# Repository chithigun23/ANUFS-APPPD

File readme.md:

# ANUFS APPPD

Accelerator pedal position (APPS) and throttle position (TPS) sensor interface for the ANUFS vehicle, with dual-redundant sensing, ignition/electronic-throttle-body kill-switch control, and CAN reporting. A single 8-pin harness connector carries power in, both raw sensor pairs, and the two kill lines out.

## Architecture

- **Power** - the LV battery feed arrives on the shared harness connector, passes through an ideal-diode PFET (Zener-biased) for reverse-polarity/surge protection, and feeds `U6` (LMR33610), which bucks it to 5V. That 5V is diode-ORed with USB-C VBUS onto a single fused node that only ever feeds `U1` (AP2112K-3.3) - the **+3.3V rail is the only supply that leaves the power stage**, reaching the MCU, CAN transceiver, both op-amps and the status LED.
- **Pedal & throttle sensing** - the harness carries two raw accelerator-pedal signals (APPS1/APPS2) and two raw throttle-position signals (TPS1/TPS2), each individually clamped by an automotive `AQ1005-01ETG` TVS array. `U5` and `U7` (`TLV9062` dual op-amps) buffer them with unity gain straight into the MCU's ADC inputs.
- **Compute** - `U2`, an STM32F072CBTx (Cortex-M0), is the hub, clocked from a 24MHz crystal (`Y1`).
- **Shutdown control** - the MCU drives two low-side MOSFETs (`Q1` for ignition, `Q2` for electronic throttle body) that pull the corresponding harness line to ground to trip the external kill relay. Each line has an inline LED (`D3`, `D5`) that lights while its kill switch is active, so the cut state is visible without a laptop. A separate GPIO-driven LED (`LED1`) gives a general board heartbeat/fault indication.
- **Comms** - a `TCAN337` transceiver (`U4`) puts pedal/throttle status and kill-line faults on the vehicle CAN bus via `J4`.
- **Debug & USB** - USB-C (`J5`, ESD-protected by `U3`) for bench debug/firmware and D+/D- to the MCU; `J1` (Conn_SWD) for programming.

The diagram above is a live SVG: dashed lines show active power/signal paths, and the small dots trace the flow through each domain (open `assets/architecture.svg` directly if your viewer doesn't animate it).

## Repo contents

- [KiCad project](apppd.kicad_pro)
- [Schematic](apppd.kicad_sch)
- [PCB layout](apppd.kicad_pcb)
- [Bill of materials](APPPD_DigiKey_BOM.xlsx)

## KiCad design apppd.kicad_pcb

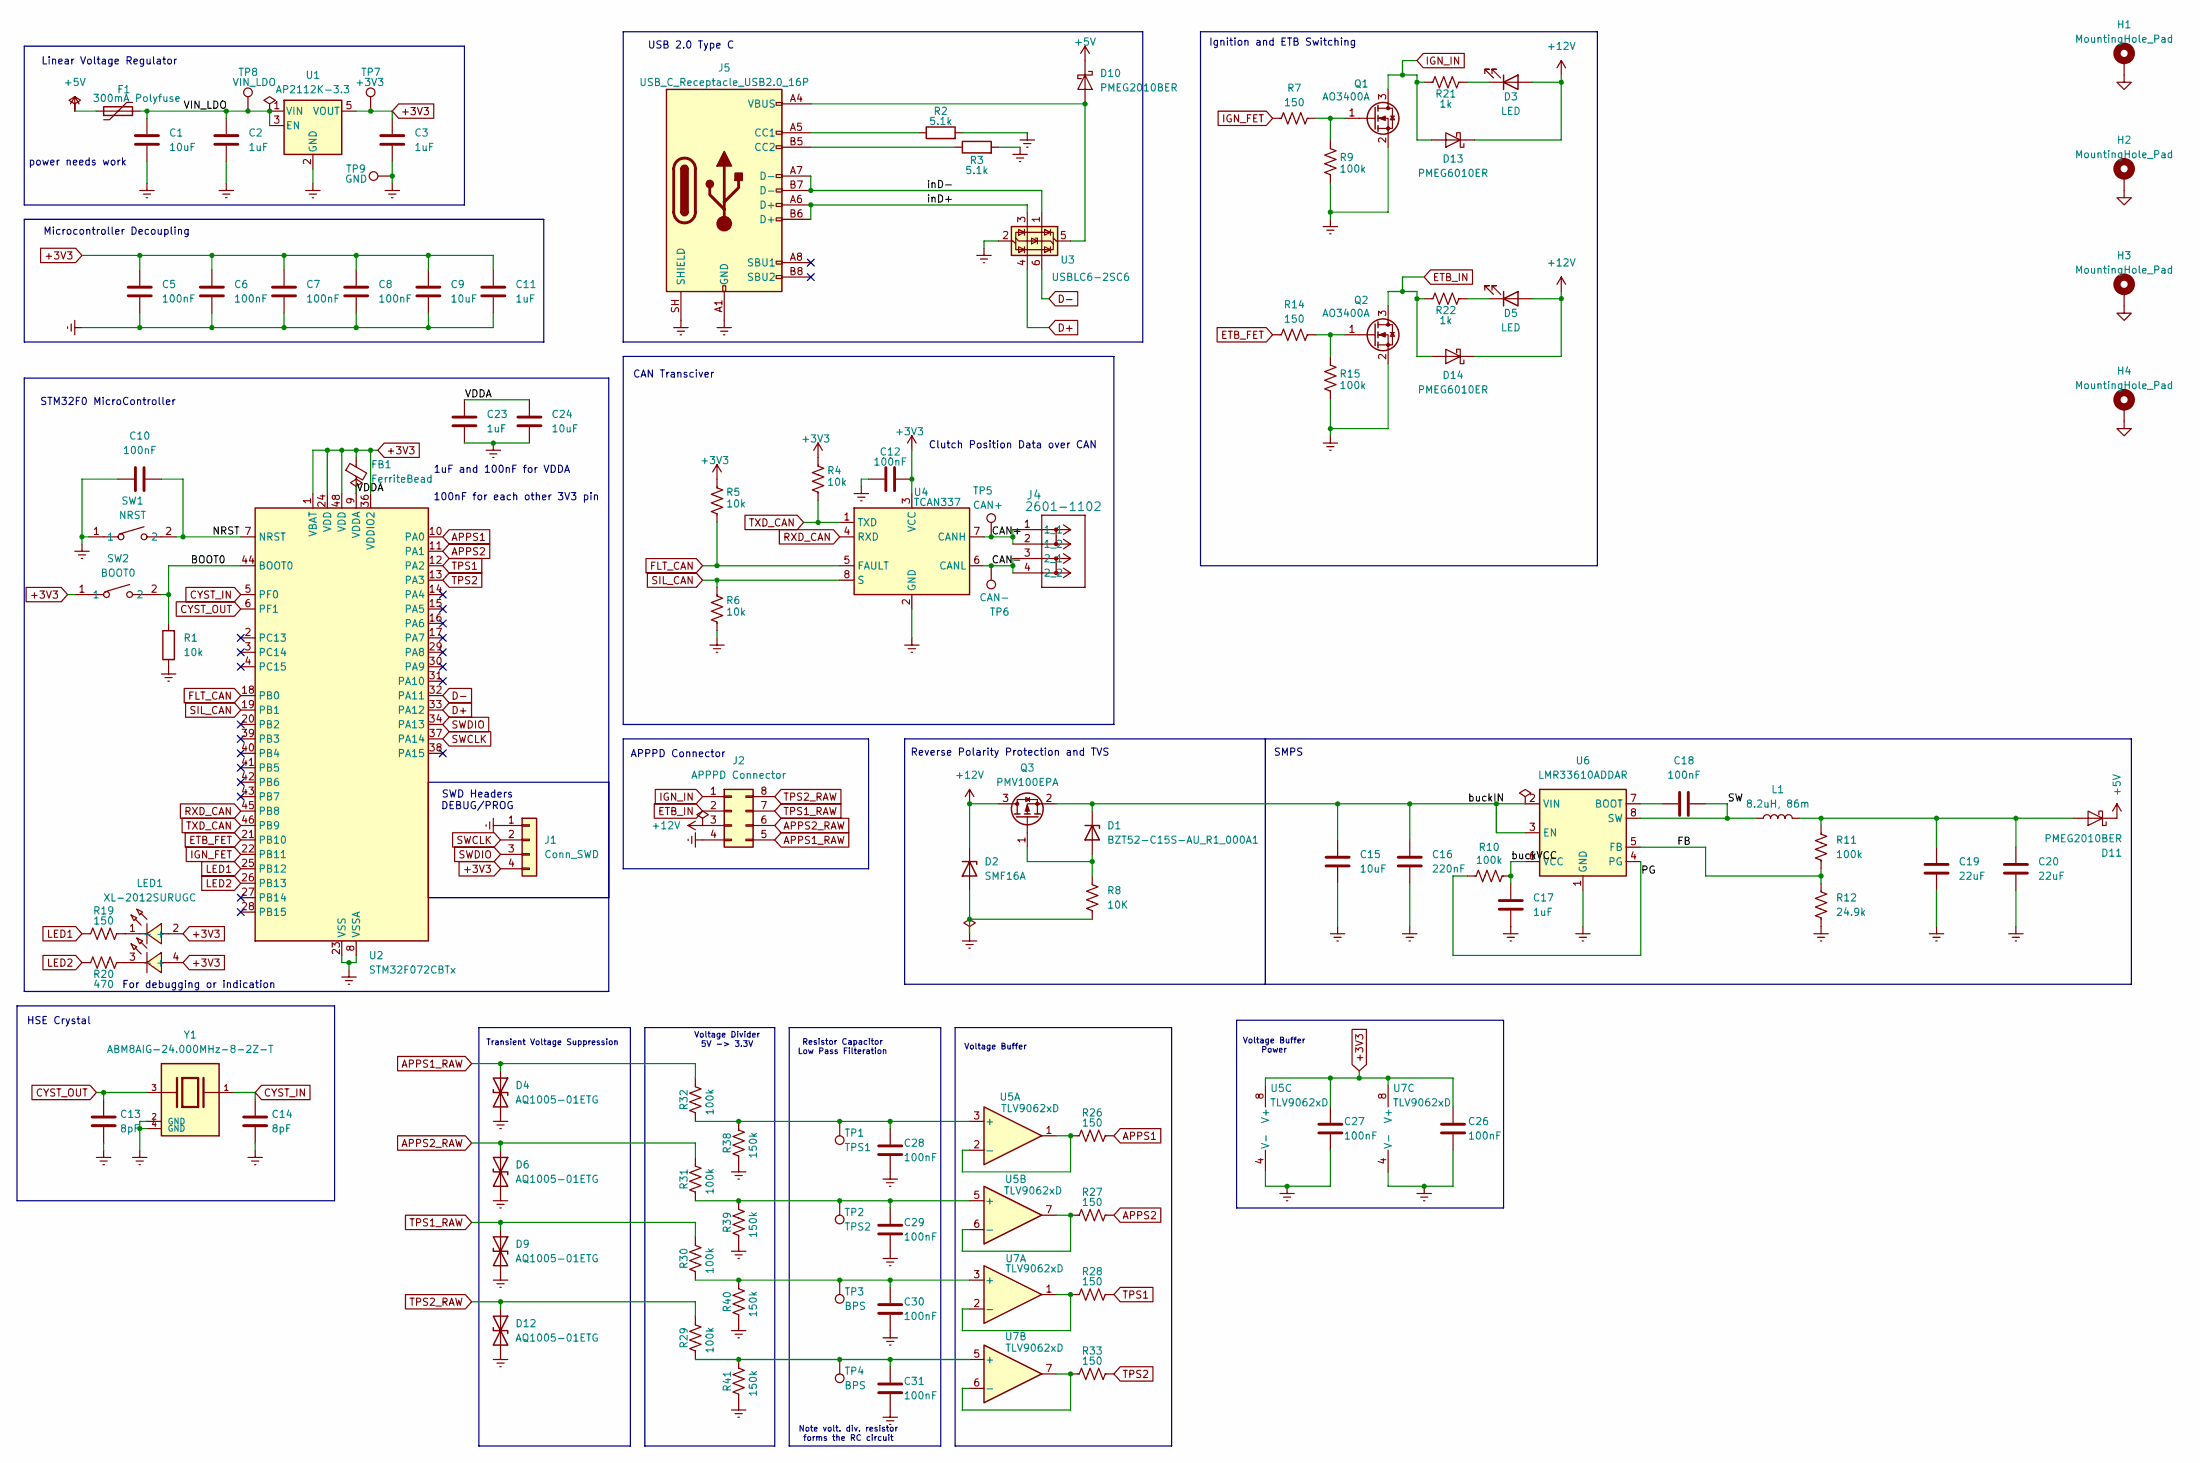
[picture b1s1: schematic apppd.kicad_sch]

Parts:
C1, C9, C15, C24: 10uF; C_0402_1005Metric_Pad0.74x0.62mm_HandSolder
C2, C3, C11, C17, C23: 1uF; C_0402_1005Metric_Pad0.74x0.62mm_HandSolder
C5, C6, C7, C8, C10, C12, C18, C26, C27, C28, C29, C30, C31: 100nF; C_0402_1005Metric_Pad0.74x0.62mm_HandSolder
C13, C14: 8pF; C_0402_1005Metric_Pad0.74x0.62mm_HandSolder
C16: 220nF; C_0402_1005Metric_Pad0.74x0.62mm_HandSolder
C19, C20: 22uF; C_0402_1005Metric_Pad0.74x0.62mm_HandSolder
D1: BZT52-C15S-AU_R1_000A1; D_SOD-323_HandSoldering
D2: SMF16A; MPN SMF16A; LCSC Part C207257
D3, D5: LED; AP2012EC
D4, D6, D9, D12: AQ1005-01ETG; MPN AQ1005-01ETG
D10, D11: PMEG2010BER; Nexperia_CFP3_SOD-123W
D13, D14: PMEG6010ER; Nexperia_CFP3_SOD-123W
F1: 300mA Polyfuse; Fuse_0805_2012Metric_Pad1.15x1.40mm_HandSolder
FB1: FerriteBead; C_0603_1608Metric_Pad1.08x0.95mm_HandSolder
H1, H2, H3, H4: MountingHole_Pad
J1: Conn_SWD; PinHeader_1x04_P2.54mm_Vertical
J2: APPPD Connector; MOLEX_430450800
J4: 2601-1102; WAGO-2601-1102
J5: USB_C_Receptacle_USB2.0_16P; USB-C-SMD_TYPE-C-16PIN-2MD-073
L1: 8.2uH, 86m; L_Vishay_IHLP-2525
LED1: XL-2012SURUGC; MPN XL-2012SURUGC; LCSC Part C965845
Q1, Q2: AO3400A; SOT-23
Q3: PMV100EPA; SOT-23
R1, R4, R5, R6: 10k; R_0402_1005Metric_Pad0.72x0.64mm_HandSolder
R2, R3: 5.1k; R_0402_1005Metric_Pad0.72x0.64mm_HandSolder
R7, R14, R19, R26, R27, R28, R33: 150; R_0402_1005Metric_Pad0.72x0.64mm_HandSolder
R8: 10K; R_0402_1005Metric_Pad0.72x0.64mm_HandSolder
R9, R10, R11, R15, R29, R30, R31, R32: 100k; R_0402_1005Metric_Pad0.72x0.64mm_HandSolder
R12: 24.9k; R_0402_1005Metric_Pad0.72x0.64mm_HandSolder
R20: 470; R_0402_1005Metric_Pad0.72x0.64mm_HandSolder
R21, R22: 1k; R_0402_1005Metric_Pad0.72x0.64mm_HandSolder
R38, R39, R40, R41: 150k; R_0402_1005Metric_Pad0.72x0.64mm_HandSolder
SW1: NRST; SW-SMD_L3.9-W3.0-P4.45; MPN TS-1088-AR02016; LCSC Part C720477
SW2: BOOT0; SW-SMD_L3.9-W3.0-P4.45; MPN TS-1088-AR02016; LCSC Part C720477
TP1: TPS1; TestPoint_Keystone_5000-5004_Miniature
TP2: TPS2; TestPoint_Keystone_5000-5004_Miniature
TP3, TP4: BPS; TestPoint_Keystone_5000-5004_Miniature
TP5: CAN+; TestPoint_THTPad_D2.0mm_Drill1.0mm
TP6: CAN-; TestPoint_THTPad_D2.0mm_Drill1.0mm
TP7: +3V3; TestPoint_THTPad_D2.0mm_Drill1.0mm
TP8: VIN_LDO; TestPoint_THTPad_D2.0mm_Drill1.0mm
TP9: GND; TestPoint_THTPad_D2.0mm_Drill1.0mm
U1: AP2112K-3.3; SOT-23-5_HandSoldering
U2: STM32F072CBTx; LQFP-48_7x7mm_P0.5mm
U3: USBLC6-2SC6; SOT-23-6
U4: TCAN337; SOIC-8_3.9x4.9mm_P1.27mm
U5, U7: TLV9062xD; SOIC-8_3.9x4.9mm_P1.27mm
U6: LMR33610ADDAR; LMR33610_HSOP8_SolidGND
Y1: ABM8AIG-24.000MHz-8-2Z-T; ABM8AIG-24.000MHZ-8-2Z-T; PARTREV 43629

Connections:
+3V3: C3.1, C5.2, C6.2, C7.2, C8.2, C9.2, C11.1, C12.2, C26.2, C27.2, FB1.1, J1.4, LED1.2 (+), LED1.4 (+), R4.1, R5.1, SW2.1, TP7.1 (1_1), U1.5 (VOUT), U2.1 (VBAT), U2.24 (VDD), U2.36 (VDDIO2), U2.48 (VDD), U4.3 (VCC), U5.8 (V+), U7.8 (V+)
+5V: D10.1 (K), D11.1 (K), F1.1
+12V: D2.1 (K), D3.2 (A), D5.2 (A), D13.1 (K), D14.1 (K), J2.3, Q3.3 (D)
/BOOT0: R1.2, SW2.2, U2.44 (BOOT0)
/CAN+: J4.1 (1_1), J4.2 (1_2), TP5.1 (1_1), U4.7 (CANH)
/CAN-: J4.3 (2_1), J4.4 (2_2), TP6.1 (1_1), U4.6 (CANL)
/FB: R11.2, R12.1, U6.5 (FB)
/NRST: C10.2, SW1.2, U2.7 (NRST)
/PG: R10.1, U6.4 (PG)
/SW: C18.2, L1.1, U6.8 (SW)
/VDDA: C23.1, C24.2, FB1.2, U2.9 (VDDA)
/VIN_LDO: C1.2, C2.1, F1.2, TP8.1 (1_1), U1.1 (VIN), U1.3 (EN)
/buckIN: C15.1, C16.1, D1.1 (K), Q3.2 (S), U6.2 (VIN), U6.3 (EN)
/buckVCC: C17.1, R10.2, U6.6 (VCC)
/inD+: J5.A6 (D+), J5.B6 (D+), U3.3 (I/O2)
/inD-: J5.A7 (D-), J5.B7 (D-), U3.1 (I/O1)
APPS1: R26.2, U2.10 (PA0)
APPS1_RAW: D4.1 (A1), J2.5, R32.2
APPS2: R27.2, U2.11 (PA1)
APPS2_RAW: D6.1 (A1), J2.6, R31.2
CYST_IN: C14.1, U2.5 (PF0), Y1.1
CYST_OUT: C13.1, U2.6 (PF1), Y1.3
D+: U2.33 (PA12), U3.4 (I/O2)
D-: U2.32 (PA11), U3.6 (I/O1)
ETB_FET: R14.1, U2.21 (PB10)
ETB_IN: D14.2 (A), J2.2, Q2.3 (D), R22.1
FLT_CAN: R5.2, U2.18 (PB0), U4.5 (FAULT)
GND: C1.1, C2.2, C3.2, C5.1, C6.1, C7.1, C8.1, C9.1, C10.1, C11.2, C12.1, C13.2, C14.2, C15.2, C16.2, C17.2, C19.2, C20.2, C23.2, C24.1, C26.1, C27.1, C28.1, C29.1, C30.1, C31.1, D2.2 (A), D4.2 (A2), D6.2 (A2), D9.2 (A2), D12.2 (A2), H1.1 (1_1), H2.1 (1_1), H3.1 (1_1), H4.1 (1_1), J1.1, J2.4, J5.A1 (GND), J5.A12 (GND), J5.B1 (GND), J5.B12 (GND), J5.SH (SHIELD), Q1.2 (S), Q2.2 (S), R1.1, R2.2, R3.2, R6.2, R8.2, R9.1, R12.2, R15.1, R38.1, R39.1, R40.1, R41.1, SW1.1, TP9.1 (1_1), U1.2 (GND), U2.8 (VSSA), U2.23 (VSS), U2.35 (VSS), U2.47 (VSS), U3.2 (GND), U4.2 (GND), U5.4 (V-), U6.1 (GND), U6.9 (GND), U7.4 (V-), Y1.2 (GND), Y1.4 (GND)
IGN_FET: R7.1, U2.22 (PB11)
IGN_IN: D13.2 (A), J2.1, Q1.3 (D), R21.1
LED1: R19.1, U2.25 (PB12)
LED2: R20.1, U2.26 (PB13)
unnamed: D1.2 (A), Q3.1 (G), R8.1
unnamed: D3.1 (K), R21.2
unnamed: D5.1 (K), R22.2
unnamed: D10.2 (A), J5.A4 (VBUS), J5.A9 (VBUS), J5.B4 (VBUS), J5.B9 (VBUS), U3.5 (VBUS)
unnamed: C19.1, C20.1, D11.2 (A), L1.2, R11.1
unnamed: J5.A5 (CC1), R2.1
unnamed: J5.B5 (CC2), R3.1
unnamed: LED1.1 (-), R19.2
unnamed: LED1.3 (-), R20.2
unnamed: Q1.1 (G), R7.2, R9.2
unnamed: Q2.1 (G), R14.2, R15.2
unnamed: C28.2, R32.1, R38.2, TP1.1 (1_1), U5.3 (+)
unnamed: R26.1, U5.1, U5.2 (-)
unnamed: C29.2, R31.1, R39.2, TP2.1 (1_1), U5.5 (+)
unnamed: R27.1, U5.6 (-), U5.7
unnamed: C18.1, U6.7 (BOOT)
unnamed: C30.2, R30.1, R40.2, TP3.1 (1_1), U7.3 (+)
unnamed: R28.1, U7.1, U7.2 (-)
unnamed: C31.2, R29.1, R41.2, TP4.1 (1_1), U7.5 (+)
unnamed: R33.1, U7.6 (-), U7.7
RXD_CAN: U2.45 (PB8), U4.4 (RXD)
SIL_CAN: R6.1, U2.19 (PB1), U4.8 (S)
SWCLK: J1.2, U2.37 (PA14)
SWDIO: J1.3, U2.34 (PA13)
TPS1: R28.2, U2.12 (PA2)
TPS1_RAW: D9.1 (A1), J2.7, R30.2
TPS2: R33.2, U2.13 (PA3)
TPS2_RAW: D12.1 (A1), J2.8, R29.2
TXD_CAN: R4.2, U2.46 (PB9), U4.1 (TXD)

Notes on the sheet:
Note volt. div. resistor forms the RC circuit
Voltage Buffer Power
Microcontroller Decoupling
Resistor Capacitor Low Pass Filteration
100nF for each other 3V3 pin
SMPS
SWD Headers DEBUG/PROG
Linear Voltage Regulator
Voltage Divider 5V -> 3.3V
Clutch Position Data over CAN
Ignition and ETB Switching
For debugging or indication
USB 2.0 Type C
APPPD Connector
HSE Crystal
Reverse Polarity Protection and TVS
Transient Voltage Suppression
1uF and 100nF for VDDA
CAN Transciver
Voltage Buffer
STM32F0 MicroController
power needs work

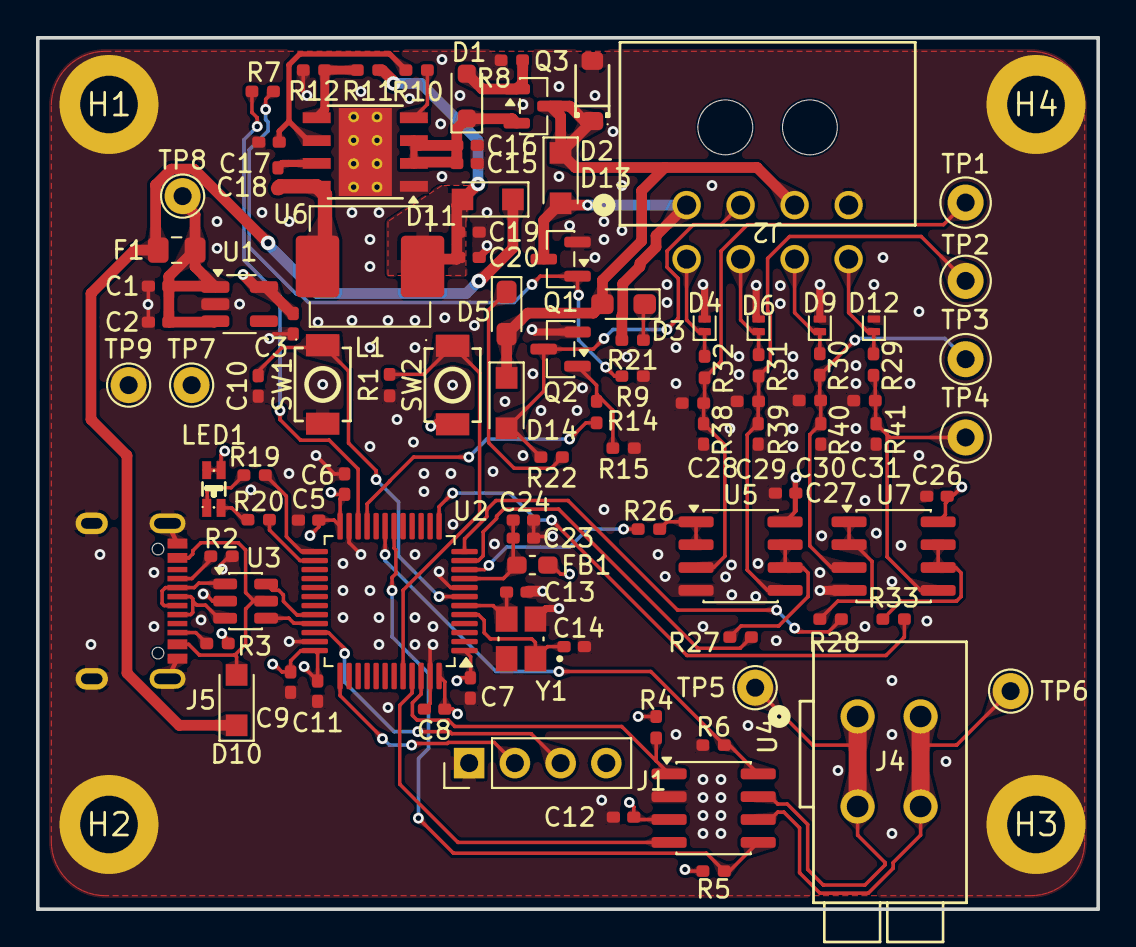
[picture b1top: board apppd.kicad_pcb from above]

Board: 4 copper layers, 58.9 x 48.4 mm, 103 parts (0 on the bottom side), 61 nets.

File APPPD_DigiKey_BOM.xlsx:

# | Reference(s) | Qty | Value | Package / Footprint | Manufacturer | Manufacturer Part Number (MPN) | DigiKey Part Number | Purchasing spec / action | Notes
1 | C1,C9,C15,C24 | 4 | 10uF | C_0402_1005Metric_Pad0.74x0.62mm_HandSolder |  |  |  | Select exact supplier part matching value and footprint.
2 | C2,C3,C11,C17,C23 | 5 | 1uF | C_0402_1005Metric_Pad0.74x0.62mm_HandSolder |  |  |  | Select exact supplier part matching value and footprint.
3 | C5-C8,C10,C12,C18,C26-C31 | 13 | 100nF | C_0402_1005Metric_Pad0.74x0.62mm_HandSolder |  |  |  | Select exact supplier part matching value and footprint.
4 | C13,C14 | 2 | 8pF | C_0402_1005Metric_Pad0.74x0.62mm_HandSolder |  |  |  | Select exact supplier part matching value and footprint.
5 | C16 | 1 | 220nF | C_0402_1005Metric_Pad0.74x0.62mm_HandSolder |  |  |  | Select exact supplier part matching value and footprint.
6 | C19,C20 | 2 | 22uF | C_0402_1005Metric_Pad0.74x0.62mm_HandSolder |  |  |  | Select exact supplier part matching value and footprint.
7 | D1 | 1 | BZT52-C15S-AU_R1_000A1 | D_SOD-323_HandSoldering |  | BZT52-C15S-AU_R1_000A1 |  | Match package and ordering suffix. | Part identifier from schematic value; verify exact ordering code.
8 | D2 | 1 | SMF16A | SMF16A | Littelfuse | SMF16A |  | Match package and ordering suffix. | LCSC: C207257
9 | D3,D5 | 2 | LED | AP2012EC |  |  |  | Select exact supplier part matching value and footprint.
10 | D4,D6,D9,D12 | 4 | AQ1005-01ETG | AQ1005-01ETG | Littelfuse | AQ1005-01ETG |  | Match package and ordering suffix.
11 | D10,D11 | 2 | PMEG2010BER | Nexperia_CFP3_SOD-123W |  | PMEG2010BER |  | Match package and ordering suffix. | Part identifier from schematic value; verify exact ordering code.
12 | D13,D14 | 2 | PMEG6010ER | Nexperia_CFP3_SOD-123W |  | PMEG6010ER |  | Match package and ordering suffix. | Part identifier from schematic value; verify exact ordering code.
13 | F1 | 1 | 300mA Polyfuse | Fuse_0805_2012Metric_Pad1.15x1.40mm_HandSolder |  |  |  | Select exact supplier part matching value and footprint.
14 | FB1 | 1 | FerriteBead | C_0603_1608Metric_Pad1.08x0.95mm_HandSolder |  |  |  | Select exact supplier part matching value and footprint.
15 | J1 | 1 | Conn_SWD | PinHeader_1x04_P2.54mm_Vertical |  |  |  | Select exact supplier part matching value and footprint.
16 | J2 | 1 | APPPD Connector | MOLEX_430450800 |  |  |  | Select exact supplier part matching value and footprint.
17 | J4 | 1 | 2601-1102 | WAGO-2601-1102 |  |  |  | Select exact supplier part matching value and footprint.
18 | J5 | 1 | USB_C_Receptacle_USB2.0_16P | USB-C-SMD_TYPE-C-16PIN-2MD-073 |  |  |  | Select exact supplier part matching value and footprint. | LCSC: C2765186
19 | L1 | 1 | 8.2uH, 86m | L_Vishay_IHLP-1616 |  |  |  | Select exact supplier part matching value and footprint.
20 | LED1 | 1 | XL-2012SURUGC | XL-2012SURUGC | XINGLIGHT(成兴光) | XL-2012SURUGC |  | Match package and ordering suffix. | LCSC: C965845
21 | Q1,Q2 | 2 | AO3400A | SOT-23 | Alpha & Omega | AO3400A |  | Match package and ordering suffix.
22 | Q3 | 1 | PMV100EPA | SOT-23 |  | PMV100EPA |  | Match package and ordering suffix. | Part identifier from schematic value; verify exact ordering code.
23 | R1,R4-R6 | 4 | 10k | R_0402_1005Metric_Pad0.72x0.64mm_HandSolder |  |  |  | Select exact supplier part matching value and footprint.
24 | R2,R3 | 2 | 5.1k | R_0402_1005Metric_Pad0.72x0.64mm_HandSolder |  |  |  | Select exact supplier part matching value and footprint.
25 | R7,R14,R19,R26-R28,R33 | 7 | 150 | R_0402_1005Metric_Pad0.72x0.64mm_HandSolder |  |  |  | Select exact supplier part matching value and footprint.
26 | R8 | 1 | 10K | R_0402_1005Metric_Pad0.72x0.64mm_HandSolder |  |  |  | Select exact supplier part matching value and footprint.
27 | R9-R11,R15,R29-R32 | 8 | 100k | R_0402_1005Metric_Pad0.72x0.64mm_HandSolder |  |  |  | Select exact supplier part matching value and footprint.
28 | R12 | 1 | 24.9k | R_0402_1005Metric_Pad0.72x0.64mm_HandSolder |  |  |  | Select exact supplier part matching value and footprint.
29 | R20 | 1 | 470 | R_0402_1005Metric_Pad0.72x0.64mm_HandSolder |  |  |  | Select exact supplier part matching value and footprint.
30 | R21,R22 | 2 | 1k | R_0402_1005Metric_Pad0.72x0.64mm_HandSolder |  |  |  | Select exact supplier part matching value and footprint.
31 | R38-R41 | 4 | 150k | R_0402_1005Metric_Pad0.72x0.64mm_HandSolder |  |  |  | Select exact supplier part matching value and footprint.
32 | SW1 | 1 | NRST | SW-SMD_L3.9-W3.0-P4.45 | XUNPU(讯普) | TS-1088-AR02016 |  | Match package and ordering suffix. | LCSC: C720477
33 | SW2 | 1 | BOOT0 | SW-SMD_L3.9-W3.0-P4.45 | XUNPU(讯普) | TS-1088-AR02016 |  | Match package and ordering suffix. | LCSC: C720477
34 | TP1 | 1 | TPS1 | TestPoint_Keystone_5000-5004_Miniature |  |  |  | Optional physical test point; select matching footprint.
35 | TP2 | 1 | TPS2 | TestPoint_Keystone_5000-5004_Miniature |  |  |  | Optional physical test point; select matching footprint.
36 | TP3,TP4 | 2 | BPS | TestPoint_Keystone_5000-5004_Miniature |  |  |  | Optional physical test point; select matching footprint.
37 | TP5 | 1 | CAN+ | TestPoint_THTPad_D2.0mm_Drill1.0mm |  |  |  | Optional physical test point; select matching footprint.
38 | TP6 | 1 | CAN- | TestPoint_THTPad_D2.0mm_Drill1.0mm |  |  |  | Optional physical test point; select matching footprint.
39 | TP7 | 1 | +3V3 | TestPoint_THTPad_D2.0mm_Drill1.0mm |  |  |  | Optional physical test point; select matching footprint.
40 | TP8 | 1 | VIN_LDO | TestPoint_THTPad_D2.0mm_Drill1.0mm |  |  |  | Optional physical test point; select matching footprint.
41 | TP9 | 1 | GND | TestPoint_THTPad_D2.0mm_Drill1.0mm |  |  |  | Optional physical test point; select matching footprint.
42 | U1 | 1 | AP2112K-3.3 | SOT-23-5_HandSoldering |  | AP2112K-3.3 |  | Match package and ordering suffix. | Part identifier from schematic value; verify exact ordering code.
43 | U2 | 1 | STM32F072CBTx | LQFP-48_7x7mm_P0.5mm |  |  |  | Select exact supplier part matching value and footprint.
44 | U3 | 1 | USBLC6-2SC6 | SOT-23-6 |  | USBLC6-2SC6 |  | Match package and ordering suffix. | Part identifier from schematic value; verify exact ordering code.
45 | U4 | 1 | TCAN337 | SOIC-8_3.9x4.9mm_P1.27mm |  | TCAN337 |  | Match package and ordering suffix. | Part identifier from schematic value; verify exact ordering code.
46 | U5,U7 | 2 | TLV9062xD | SOIC-8_3.9x4.9mm_P1.27mm |  |  |  | Select exact supplier part matching value and footprint.
47 | U6 | 1 | LMR33610ADDAR | LMR33610_HSOP8_SolidGND |  | LMR33610ADDAR |  | Match package and ordering suffix. | Part identifier from schematic value; verify exact ordering code.
48 | Y1 | 1 | ABM8AIG-24.000MHz-8-2Z-T | ABM8AIG-24.000MHZ-8-2Z-T | Abracon | ABM8AIG-24.000MHz-8-2Z-T |  | Match package and ordering suffix. | Part identifier from schematic value; verify exact ordering code.
 | TOTAL PLACEMENTS | 99
